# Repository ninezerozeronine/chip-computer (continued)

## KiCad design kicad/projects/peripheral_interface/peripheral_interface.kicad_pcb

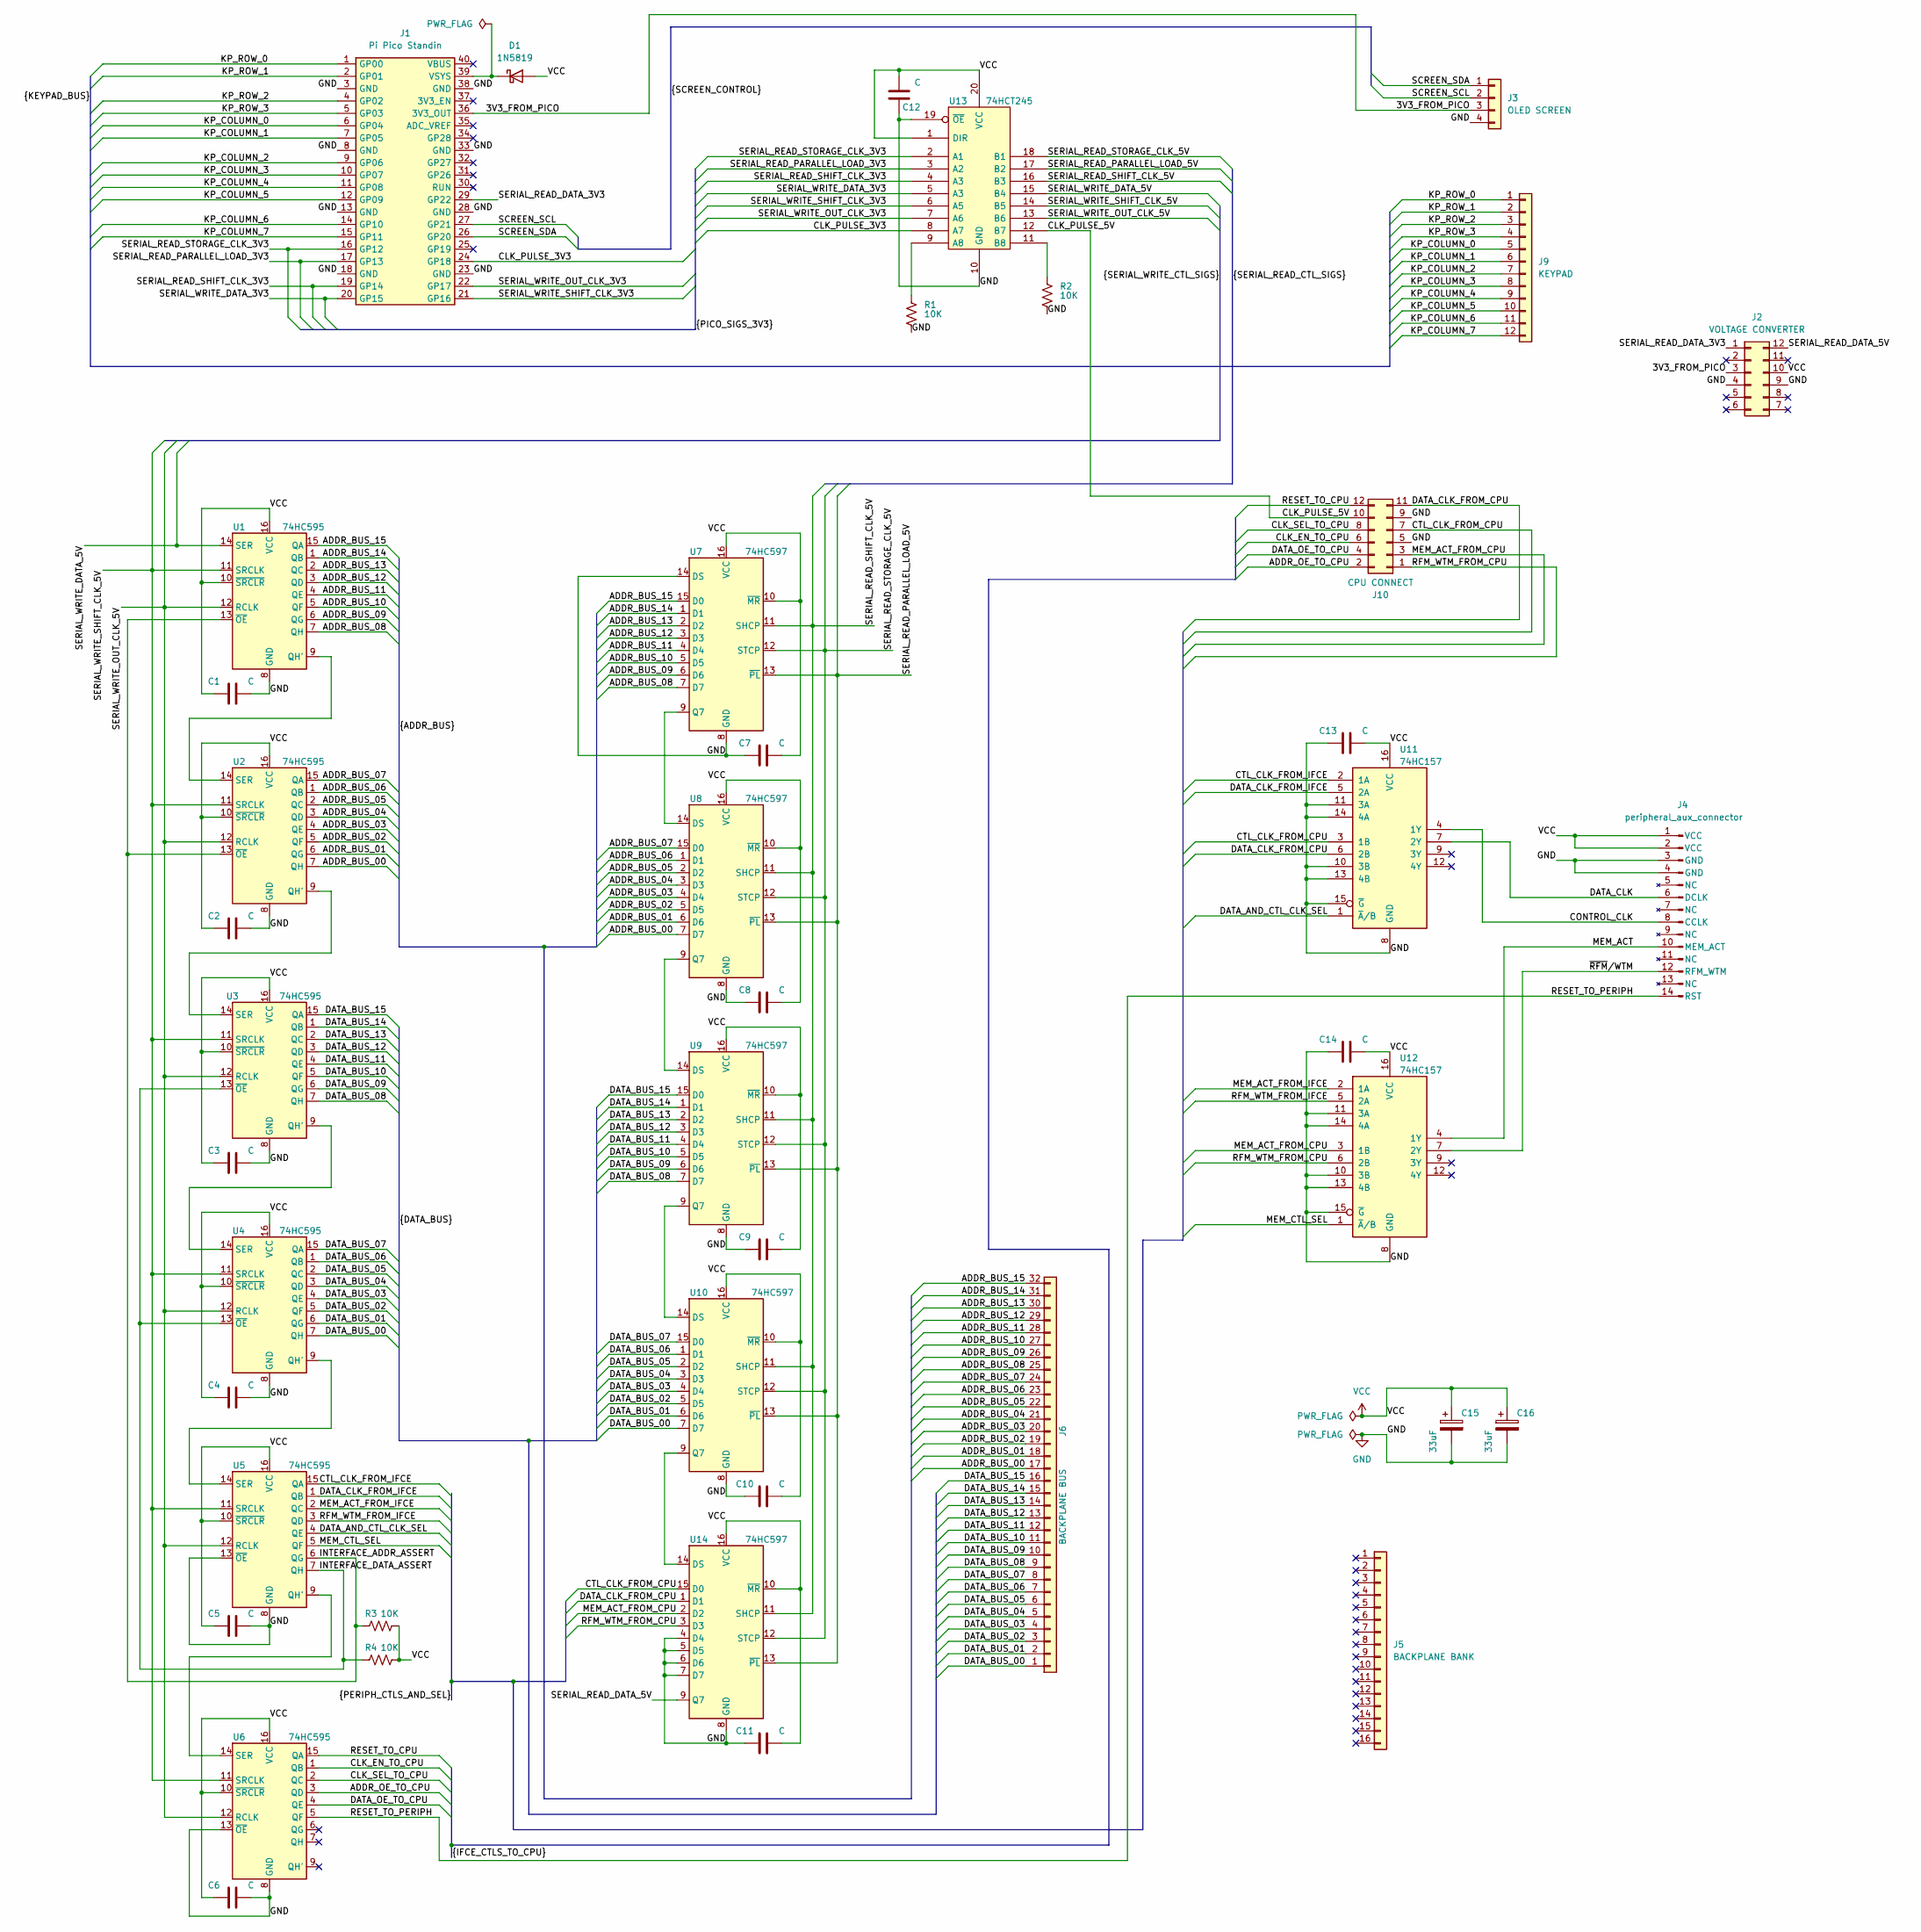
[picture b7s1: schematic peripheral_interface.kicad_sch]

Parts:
C1, C2, C3, C4, C5, C6, C7, C8, C9, C10, C11, C12, C13, C14: C; C_Disc_D4.7mm_W2.5mm_P5.00mm
C15, C16: 33uF; CP_Radial_D6.3mm_P2.50mm
D1: 1N5819; D_DO-41_SOD81_P10.16mm_Horizontal
J1: Pi Pico Standin; pi-pico-standin
J2: VOLTAGE CONVERTER; voltage-level-converter
J3: OLED SCREEN; mini-oled-screen
J4: peripheral_aux_connector; peripheral-backplane-aux
J5: BACKPLANE BANK; peripheral-backplane-membank
J6: BACKPLANE BUS; peripheral-backplane-data-addr-anno
J9: KEYPAD; PinSocket_1x12_P2.54mm_Vertical
J10: CPU CONNECT; PinSocket_2x06_P2.54mm_Horizontal
R1, R2: 10K; R_Axial_DIN0207_L6.3mm_D2.5mm_P10.16mm_Horizontal
R3, R4: 10K; R_Axial_DIN0207_L6.3mm_D2.5mm_P2.54mm_Vertical
U1, U2, U3, U4, U5, U6: 74HC595; DIP-16_W7.62mm_Socket
U7, U8, U9, U10, U14: 74HC597; DIP-16_W7.62mm_Socket
U11, U12: 74HC157; DIP-16_W7.62mm_Socket
U13: 74HCT245; DIP-20_W7.62mm_Socket

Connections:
/3V3_FROM_PICO: J1.36 (3V3_OUT), J2.3, J3.3
/ADDR_BUS_00: J6.17, U2.7 (QH), U8.7 (D7)
/ADDR_BUS_01: J6.18, U2.6 (QG), U8.6 (D6)
/ADDR_BUS_02: J6.19, U2.5 (QF), U8.5 (D5)
/ADDR_BUS_03: J6.20, U2.4 (QE), U8.4 (D4)
/ADDR_BUS_04: J6.21, U2.3 (QD), U8.3 (D3)
/ADDR_BUS_05: J6.22, U2.2 (QC), U8.2 (D2)
/ADDR_BUS_06: J6.23, U2.1 (QB), U8.1 (D1)
/ADDR_BUS_07: J6.24, U2.15 (QA), U8.15 (D0)
/ADDR_BUS_08: J6.25, U1.7 (QH), U7.7 (D7)
/ADDR_BUS_09: J6.26, U1.6 (QG), U7.6 (D6)
/ADDR_BUS_10: J6.27, U1.5 (QF), U7.5 (D5)
/ADDR_BUS_11: J6.28, U1.4 (QE), U7.4 (D4)
/ADDR_BUS_12: J6.29, U1.3 (QD), U7.3 (D3)
/ADDR_BUS_13: J6.30, U1.2 (QC), U7.2 (D2)
/ADDR_BUS_14: J6.31, U1.1 (QB), U7.1 (D1)
/ADDR_BUS_15: J6.32, U1.15 (QA), U7.15 (D0)
/ADDR_OE_TO_CPU: J10.2, U6.3 (QD)
/CLK_EN_TO_CPU: J10.6, U6.1 (QB)
/CLK_PULSE_3V3: J1.24 (GP18), U13.8 (A7)
/CLK_PULSE_5V: J10.10, U13.12 (B7)
/CLK_SEL_TO_CPU: J10.8, U6.2 (QC)
/CONTROL_CLK: J4.8 (CCLK), U11.4 (1Y)
/CTL_CLK_FROM_CPU: J10.7, U11.3 (1B), U14.15 (D0)
/CTL_CLK_FROM_IFCE: U5.15 (QA), U11.2 (1A)
/DATA_AND_CTL_CLK_SEL: U5.4 (QE), U11.1 (~A/B)
/DATA_BUS_00: J6.1, U4.7 (QH), U10.7 (D7)
/DATA_BUS_01: J6.2, U4.6 (QG), U10.6 (D6)
/DATA_BUS_02: J6.3, U4.5 (QF), U10.5 (D5)
/DATA_BUS_03: J6.4, U4.4 (QE), U10.4 (D4)
/DATA_BUS_04: J6.5, U4.3 (QD), U10.3 (D3)
/DATA_BUS_05: J6.6, U4.2 (QC), U10.2 (D2)
/DATA_BUS_06: J6.7, U4.1 (QB), U10.1 (D1)
/DATA_BUS_07: J6.8, U4.15 (QA), U10.15 (D0)
/DATA_BUS_08: J6.9, U3.7 (QH), U9.7 (D7)
/DATA_BUS_09: J6.10, U3.6 (QG), U9.6 (D6)
/DATA_BUS_10: J6.11, U3.5 (QF), U9.5 (D5)
/DATA_BUS_11: J6.12, U3.4 (QE), U9.4 (D4)
/DATA_BUS_12: J6.13, U3.3 (QD), U9.3 (D3)
/DATA_BUS_13: J6.14, U3.2 (QC), U9.2 (D2)
/DATA_BUS_14: J6.15, U3.1 (QB), U9.1 (D1)
/DATA_BUS_15: J6.16, U3.15 (QA), U9.15 (D0)
/DATA_CLK: J4.6 (DCLK), U11.7 (2Y)
/DATA_CLK_FROM_CPU: J10.11, U11.6 (2B), U14.1 (D1)
/DATA_CLK_FROM_IFCE: U5.1 (QB), U11.5 (2A)
/DATA_OE_TO_CPU: J10.4, U6.4 (QE)
/INTERFACE_ADDR_ASSERT: R3.1, U1.13 (~OE), U2.13 (~OE), U5.6 (QG)
/INTERFACE_DATA_ASSERT: R4.1, U3.13 (~OE), U4.13 (~OE), U5.7 (QH)
/KP_COLUMN_0: J1.6 (GP04), J9.5
/KP_COLUMN_1: J1.7 (GP05), J9.6
/KP_COLUMN_2: J1.9 (GP06), J9.7
/KP_COLUMN_3: J1.10 (GP07), J9.8
/KP_COLUMN_4: J1.11 (GP08), J9.9
/KP_COLUMN_5: J1.12 (GP09), J9.10
/KP_COLUMN_6: J1.14 (GP10), J9.11
/KP_COLUMN_7: J1.15 (GP11), J9.12
/KP_ROW_0: J1.1 (GP00), J9.1
/KP_ROW_1: J1.2 (GP01), J9.2
/KP_ROW_2: J1.4 (GP02), J9.3
/KP_ROW_3: J1.5 (GP03), J9.4
/MEM_ACT: J4.10 (MEM_ACT), U12.4 (1Y)
/MEM_ACT_FROM_CPU: J10.3, U12.3 (1B), U14.2 (D2)
/MEM_ACT_FROM_IFCE: U5.2 (QC), U12.2 (1A)
/MEM_CTL_SEL: U5.5 (QF), U12.1 (~A/B)
/RESET_TO_CPU: J10.12, U6.15 (QA)
/RESET_TO_PERIPH: J4.14 (RST), U6.5 (QF)
/RFM_WTM_FROM_CPU: J10.1, U12.6 (2B), U14.3 (D3)
/RFM_WTM_FROM_IFCE: U5.3 (QD), U12.5 (2A)
/SCREEN_SCL: J1.27 (GP21), J3.2
/SCREEN_SDA: J1.26 (GP20), J3.1
/SERIAL_READ_DATA_3V3: J1.29 (GP22), J2.1
/SERIAL_READ_DATA_5V: J2.12, U14.9 (Q7)
/SERIAL_READ_PARALLEL_LOAD_3V3: J1.17 (GP13), U13.3 (A2)
/SERIAL_READ_PARALLEL_LOAD_5V: U7.13 (~PL), U8.13 (~PL), U9.13 (~PL), U10.13 (~PL), U13.17 (B2), U14.13 (~PL)
/SERIAL_READ_SHIFT_CLK_3V3: J1.19 (GP14), U13.4 (A3)
/SERIAL_READ_SHIFT_CLK_5V: U7.11 (SHCP), U8.11 (SHCP), U9.11 (SHCP), U10.11 (SHCP), U13.16 (B3), U14.11 (SHCP)
/SERIAL_READ_STORAGE_CLK_3V3: J1.16 (GP12), U13.2 (A1)
/SERIAL_READ_STORAGE_CLK_5V: U7.12 (STCP), U8.12 (STCP), U9.12 (STCP), U10.12 (STCP), U13.18 (B1), U14.12 (STCP)
/SERIAL_WRITE_DATA_3V3: J1.20 (GP15), U13.5 (A3)
/SERIAL_WRITE_DATA_5V: U1.14 (SER), U13.15 (B4)
/SERIAL_WRITE_OUT_CLK_3V3: J1.22 (GP17), U13.7 (A6)
/SERIAL_WRITE_OUT_CLK_5V: U1.12 (RCLK), U2.12 (RCLK), U3.12 (RCLK), U4.12 (RCLK), U5.12 (RCLK), U6.12 (RCLK), U13.13 (B6)
/SERIAL_WRITE_SHIFT_CLK_3V3: J1.21 (GP16), U13.6 (A5)
/SERIAL_WRITE_SHIFT_CLK_5V: U1.11 (SRCLK), U2.11 (SRCLK), U3.11 (SRCLK), U4.11 (SRCLK), U5.11 (SRCLK), U6.11 (SRCLK), U13.14 (B5)
/~RFM/WTM: J4.12 (RFM_WTM), U12.7 (2Y)
GND: C1.2, C2.2, C3.2, C4.2, C5.2, C6.2, C7.1, C8.1, C9.1, C10.1, C11.1, C12.1, C13.1, C14.1, C15.2, C16.2, J1.3 (GND), J1.8 (GND), J1.13 (GND), J1.18 (GND), J1.23 (GND), J1.28 (GND), J1.33 (GND), J1.38 (GND), J2.4, J2.9, J3.4, J4.3 (GND), J4.4 (GND), J10.5, J10.9, R1.2, R2.2, U1.8 (GND), U2.8 (GND), U3.8 (GND), U4.8 (GND), U5.8 (GND), U5.13 (~OE), U6.8 (GND), U6.13 (~OE), U7.8 (GND), U7.14 (DS), U8.8 (GND), U9.8 (GND), U10.8 (GND), U11.8 (GND), U11.10 (3B), U11.11 (3A), U11.13 (4B), U11.14 (4A), U11.15 (~G), U12.8 (GND), U12.10 (3B), U12.11 (3A), U12.13 (4B), U12.14 (4A), U12.15 (~G), U13.10 (GND), U13.19 (~OE), U14.4 (D4), U14.5 (D5), U14.6 (D6), U14.7 (D7), U14.8 (GND)
unnamed: D1.1 (K), J1.39 (VSYS)
unnamed: U1.9 (QH'), U2.14 (SER)
unnamed: U2.9 (QH'), U3.14 (SER)
unnamed: U3.9 (QH'), U4.14 (SER)
unnamed: U4.9 (QH'), U5.14 (SER)
unnamed: U5.9 (QH'), U6.14 (SER)
unnamed: U7.9 (Q7), U8.14 (DS)
unnamed: U8.9 (Q7), U9.14 (DS)
unnamed: U9.9 (Q7), U10.14 (DS)
unnamed: U10.9 (Q7), U14.14 (DS)
unnamed: R1.1, U13.9 (A8)
unnamed: R2.1, U13.11 (B8)
VCC: C1.1, C2.1, C3.1, C4.1, C5.1, C6.1, C7.2, C8.2, C9.2, C10.2, C11.2, C12.2, C13.2, C14.2, C15.1, C16.1, D1.2 (A), J2.10, J4.1 (VCC), J4.2 (VCC), R3.2, R4.2, U1.10 (~SRCLR), U1.16 (VCC), U2.10 (~SRCLR), U2.16 (VCC), U3.10 (~SRCLR), U3.16 (VCC), U4.10 (~SRCLR), U4.16 (VCC), U5.10 (~SRCLR), U5.16 (VCC), U6.10 (~SRCLR), U6.16 (VCC), U7.10 (~MR), U7.16 (VCC), U8.10 (~MR), U8.16 (VCC), U9.10 (~MR), U9.16 (VCC), U10.10 (~MR), U10.16 (VCC), U11.16 (VCC), U12.16 (VCC), U13.1 (DIR), U13.20 (VCC), U14.10 (~MR), U14.16 (VCC)

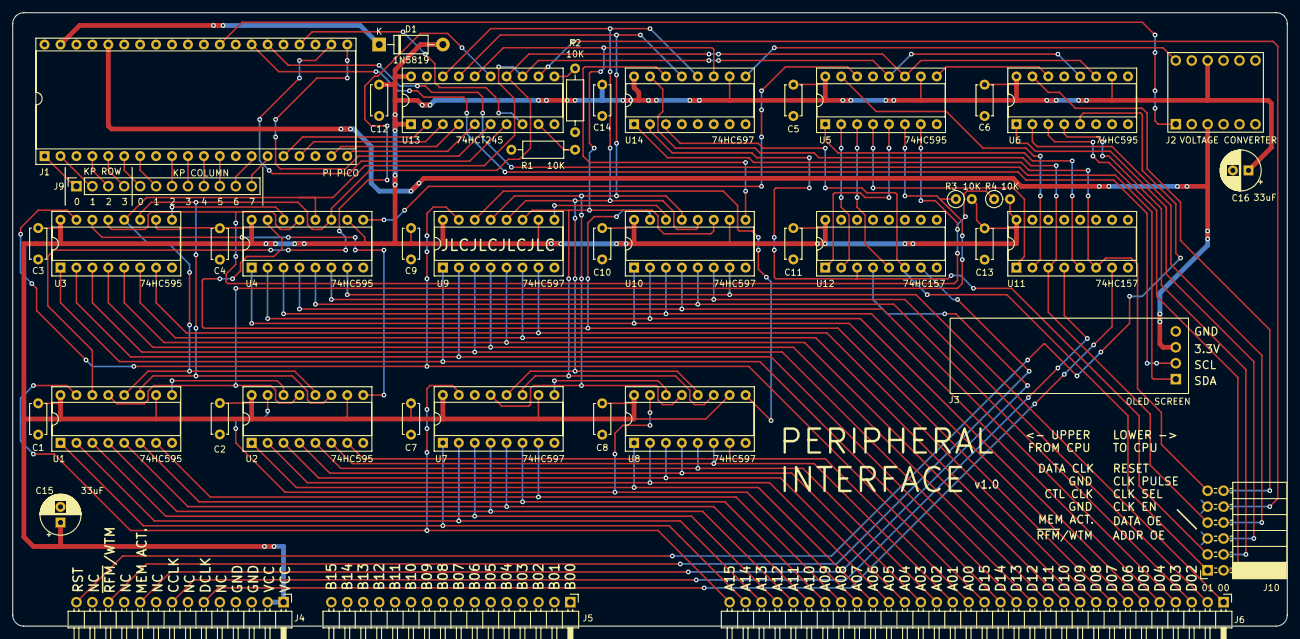
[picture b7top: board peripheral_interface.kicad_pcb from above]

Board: 2 copper layers, 203.2 x 97.8 mm, 43 parts (0 on the bottom side), 99 nets.

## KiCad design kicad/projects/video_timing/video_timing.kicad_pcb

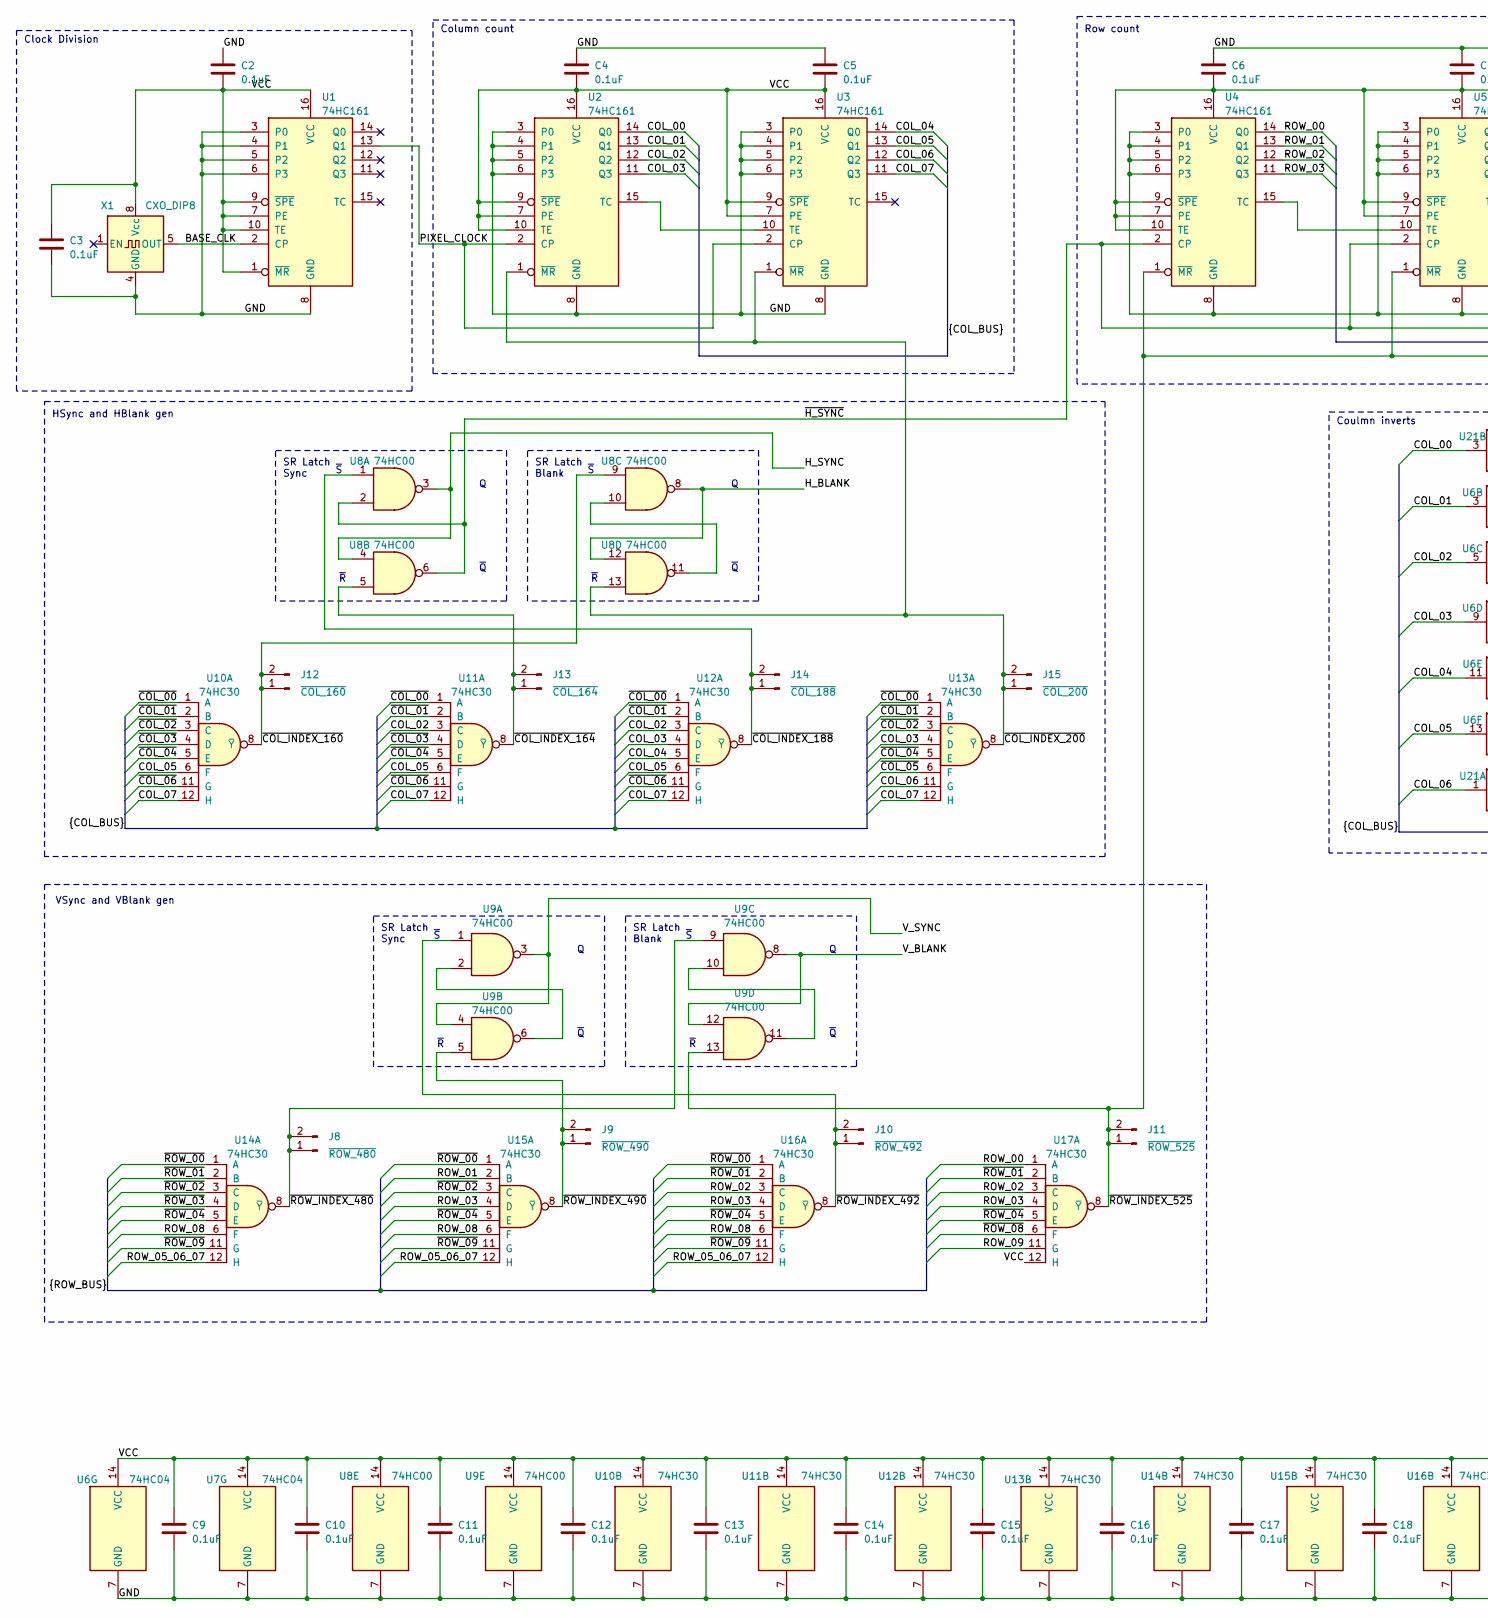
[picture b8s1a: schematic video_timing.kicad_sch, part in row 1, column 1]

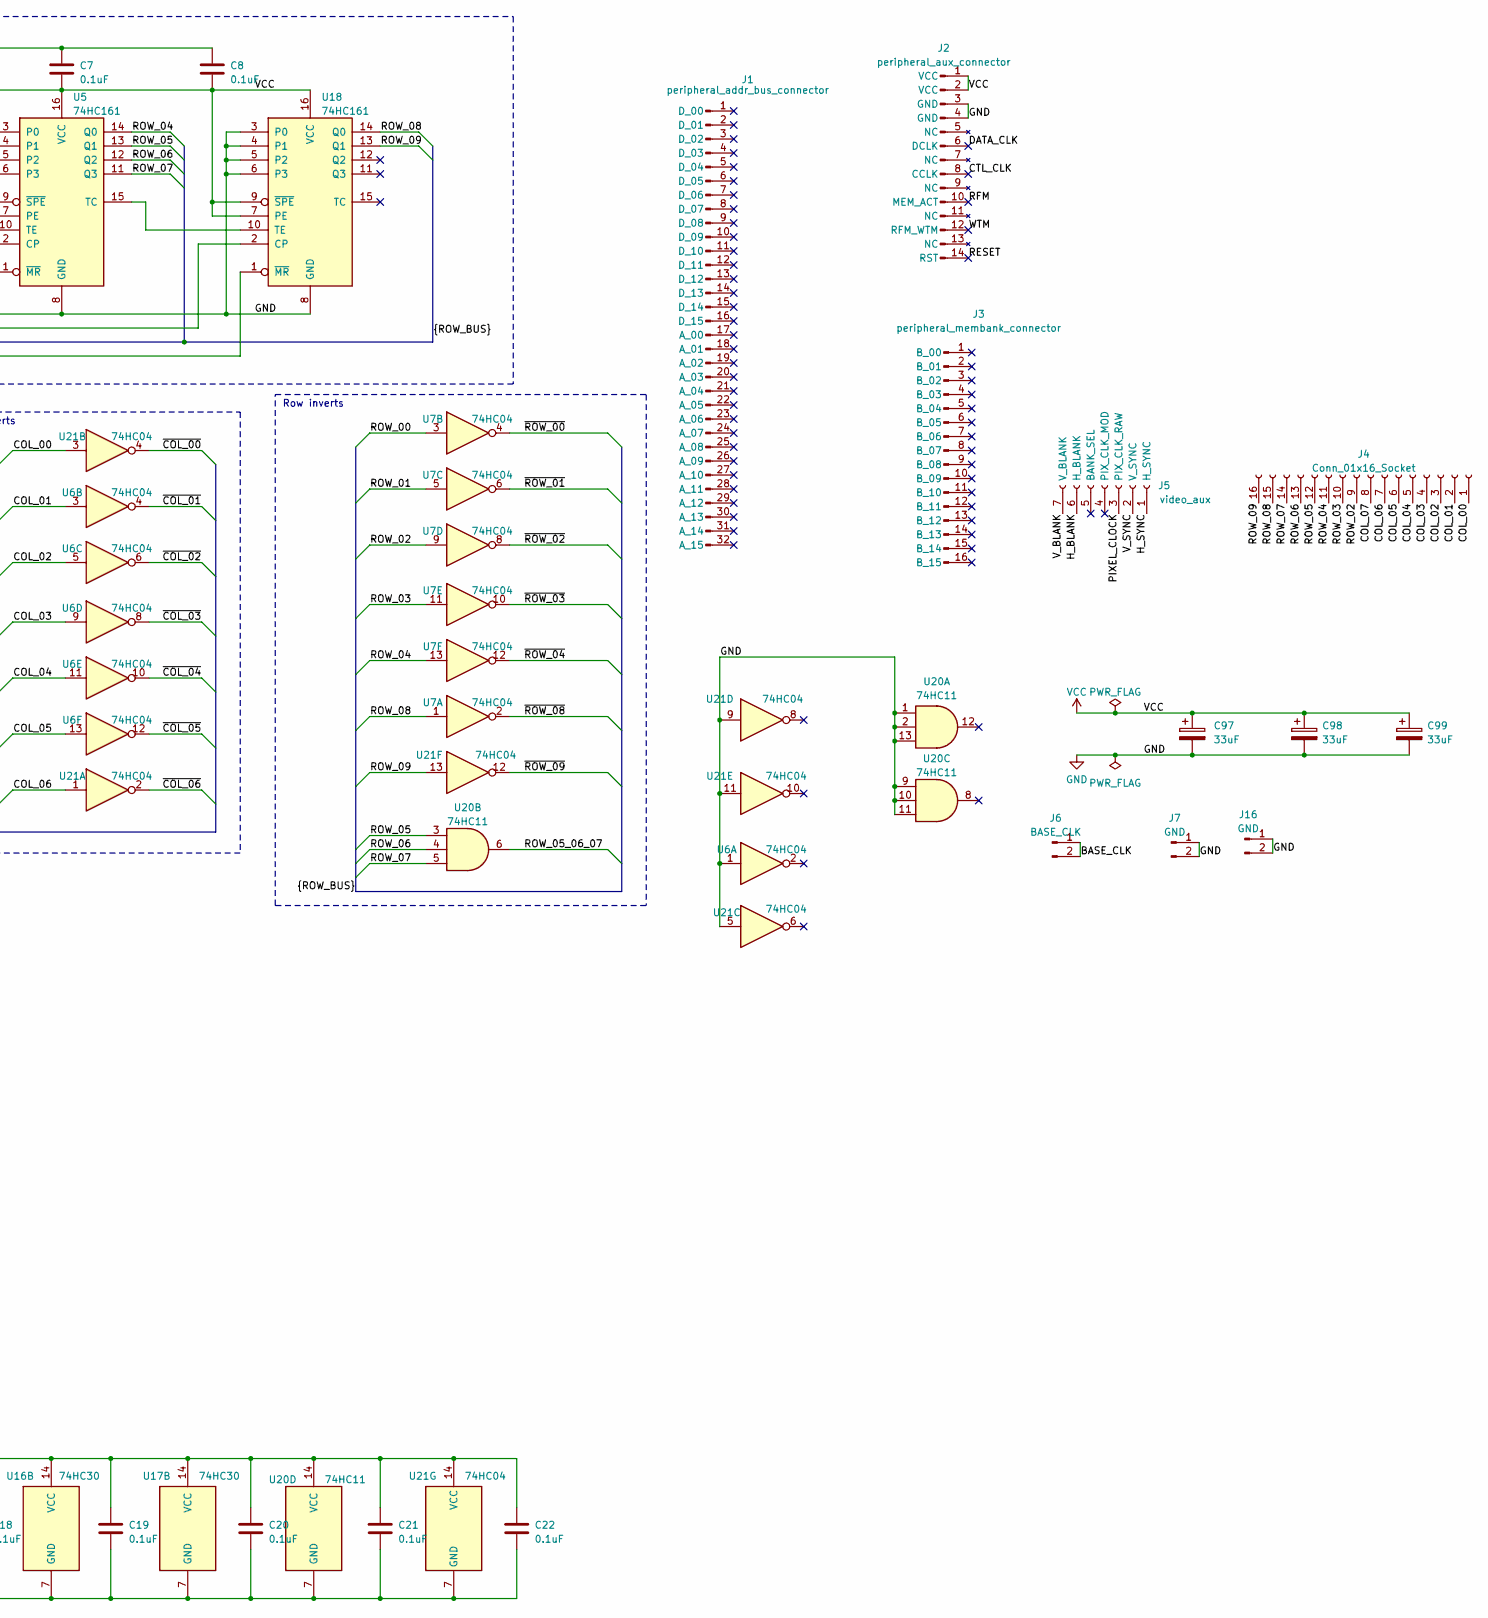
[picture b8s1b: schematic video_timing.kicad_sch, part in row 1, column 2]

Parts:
C2, C3, C4, C5, C6, C7, C8, C9, C10, C11, C12, C13, C14, C15, C16, C17, C18, C19, C20, C21, C22: 0.1uF; C_Disc_D5.0mm_W2.5mm_P5.00mm
C97, C98, C99: 33uF; CP_Radial_D6.3mm_P2.50mm
J1: peripheral_addr_bus_connector; peripheral-backplane-data-addr-anno
J2: peripheral_aux_connector; peripheral-backplane-aux
J3: peripheral_membank_connector; peripheral-backplane-membank
J4: Conn_01x16_Socket; PinSocket_1x16_P2.54mm_Horizontal
J5: video_aux; PinSocket_1x07_P2.54mm_Horizontal
J6: BASE_CLK; PinHeader_1x02_P2.54mm_Vertical
J7, J16: GND; PinHeader_1x02_P2.54mm_Vertical
J8: ~{ROW_480}; PinHeader_1x02_P2.54mm_Vertical
J9: ~{ROW_490}; PinHeader_1x02_P2.54mm_Vertical
J10: ~{ROW_492}; PinHeader_1x02_P2.54mm_Vertical
J11: ~{ROW_525}; PinHeader_1x02_P2.54mm_Vertical
J12: ~{COL_160}; PinHeader_1x02_P2.54mm_Vertical
J13: ~{COL_164}; PinHeader_1x02_P2.54mm_Vertical
J14: ~{COL_188}; PinHeader_1x02_P2.54mm_Vertical
J15: ~{COL_200}; PinHeader_1x02_P2.54mm_Vertical
U1, U2, U3, U4, U5, U18: 74HC161; DIP-16_W7.62mm_Socket
U6, U7, U21: 74HC04; DIP-14_W7.62mm_Socket
U8, U9: 74HC00; DIP-14_W7.62mm_Socket
U10, U11, U12, U13, U14, U15, U16, U17: 74HC30; DIP-14_W7.62mm_Socket
U20: 74HC11; DIP-14_W7.62mm_Socket
X1: CXO_DIP8; Oscillator_DIP-8

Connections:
/BASE_CLK: J6.1, J6.2, U1.2 (CP), X1.5 (OUT)
/COL_00: J4.1, U2.14 (Q0), U21.3
/COL_01: J4.2, U2.13 (Q1), U6.3
/COL_02: J4.3, U2.12 (Q2), U6.5, U11.3 (C), U12.3 (C)
/COL_03: J4.4, U2.11 (Q3), U6.9, U12.4 (D), U13.4 (D)
/COL_04: J4.5, U3.14 (Q0), U6.11, U12.5 (E)
/COL_05: J4.6, U3.13 (Q1), U6.13, U10.6 (F), U11.6 (F), U12.6 (F)
/COL_06: J4.7, U3.12 (Q2), U13.11 (G), U21.1
/COL_07: J4.8, U3.11 (Q3), U10.12 (H), U11.12 (H), U12.12 (H), U13.12 (H)
/CTL_CLK: J2.8 (CCLK)
/DATA_CLK: J2.6 (DCLK)
/H_BLANK: J5.6 (H_BLANK), U8.8, U8.12
/H_SYNC: J5.1 (H_SYNC), U8.3, U8.4
/PIXEL_CLOCK: J5.3 (PIX_CLK_RAW), U1.13 (Q1), U2.2 (CP), U3.2 (CP)
/RESET: J2.14 (RST)
/RFM: J2.10 (MEM_ACT)
/ROW_00: U4.14 (Q0), U7.3, U17.1 (A)
/ROW_01: U4.13 (Q1), U7.5, U15.2 (B)
/ROW_02: J4.9, U4.12 (Q2), U7.9, U16.3 (C), U17.3 (C)
/ROW_03: J4.10, U4.11 (Q3), U7.11, U15.4 (D), U16.4 (D), U17.4 (D)
/ROW_04: J4.11, U5.14 (Q0), U7.13
/ROW_05: J4.12, U5.13 (Q1), U20.3
/ROW_05_06_07: U14.12 (H), U15.12 (H), U16.12 (H), U20.6
/ROW_06: J4.13, U5.12 (Q2), U20.4
/ROW_07: J4.14, U5.11 (Q3), U20.5
/ROW_08: J4.15, U7.1, U14.6 (F), U15.6 (F), U16.6 (F), U18.14 (Q0)
/ROW_09: J4.16, U17.11 (G), U18.13 (Q1), U21.13
/V_BLANK: J5.7 (V_BLANK), U9.8, U9.12
/V_SYNC: J5.2 (V_SYNC), U9.3, U9.4
/WTM: J2.12 (RFM_WTM)
/~COL_00: U10.1 (A), U11.1 (A), U12.1 (A), U13.1 (A), U21.4
/~COL_01: U6.4, U10.2 (B), U11.2 (B), U12.2 (B), U13.2 (B)
/~COL_02: U6.6, U10.3 (C), U13.3 (C)
/~COL_03: U6.8, U10.4 (D), U11.4 (D)
/~COL_04: U6.10, U10.5 (E), U11.5 (E), U13.5 (E)
/~COL_05: U6.12, U13.6 (F)
/~COL_06: U10.11 (G), U11.11 (G), U12.11 (G), U21.2
/~COL_INDEX_160: J12.1, J12.2, U8.9, U10.8 (~Y)
/~COL_INDEX_164: J13.1, J13.2, U8.5, U11.8 (~Y)
/~COL_INDEX_188: J14.1, J14.2, U8.1, U12.8 (~Y)
/~COL_INDEX_200: J15.1, J15.2, U2.1 (~MR), U3.1 (~MR), U8.13, U13.8 (~Y)
/~H_SYNC: U4.2 (CP), U5.2 (CP), U8.2, U8.6, U18.2 (CP)
/~ROW_00: U7.4, U14.1 (A), U15.1 (A), U16.1 (A)
/~ROW_01: U7.6, U14.2 (B), U16.2 (B), U17.2 (B)
/~ROW_02: U7.8, U14.3 (C), U15.3 (C)
/~ROW_03: U7.10, U14.4 (D)
/~ROW_04: U7.12, U14.5 (E), U15.5 (E), U16.5 (E), U17.5 (E)
/~ROW_08: U7.2, U17.6 (F)
/~ROW_09: U14.11 (G), U15.11 (G), U16.11 (G), U21.12
/~ROW_INDEX_480: J8.1, J8.2, U9.9, U14.8 (~Y)
/~ROW_INDEX_490: J9.1, J9.2, U9.5, U15.8 (~Y)
/~ROW_INDEX_492: J10.1, J10.2, U9.1, U16.8 (~Y)
/~ROW_INDEX_525: J11.1, J11.2, U4.1 (~MR), U5.1 (~MR), U9.13, U17.8 (~Y), U18.1 (~MR)
GND: C2.1, C3.2, C4.1, C5.1, C6.1, C7.1, C8.1, C9.2, C10.2, C11.2, C12.2, C13.2, C14.2, C15.2, C16.2, C17.2, C18.2, C19.2, C20.2, C21.2, C22.2, C97.2, C98.2, C99.2, J2.3 (GND), J2.4 (GND), J7.1, J7.2, J16.1, J16.2, U1.3 (P0), U1.4 (P1), U1.5 (P2), U1.6 (P3), U1.8 (GND), U2.3 (P0), U2.4 (P1), U2.5 (P2), U2.6 (P3), U2.8 (GND), U3.3 (P0), U3.4 (P1), U3.5 (P2), U3.6 (P3), U3.8 (GND), U4.3 (P0), U4.4 (P1), U4.5 (P2), U4.6 (P3), U4.8 (GND), U5.3 (P0), U5.4 (P1), U5.5 (P2), U5.6 (P3), U5.8 (GND), U6.1, U6.7 (GND), U7.7 (GND), U8.7 (GND), U9.7 (GND), U10.7 (GND), U11.7 (GND), U12.7 (GND), U13.7 (GND), U14.7 (GND), U15.7 (GND), U16.7 (GND), U17.7 (GND), U18.3 (P0), U18.4 (P1), U18.5 (P2), U18.6 (P3), U18.8 (GND), U20.1, U20.2, U20.7 (GND), U20.9, U20.10, U20.11, U20.13, U21.5, U21.7 (GND), U21.9, U21.11, X1.4 (GND)
unnamed: U2.15 (TC), U3.10 (TE)
unnamed: U4.15 (TC), U5.10 (TE)
unnamed: U8.10, U8.11
unnamed: U9.2, U9.6
unnamed: U9.10, U9.11
unnamed: U5.15 (TC), U18.10 (TE)
VCC: C2.2, C3.1, C4.2, C5.2, C6.2, C7.2, C8.2, C9.1, C10.1, C11.1, C12.1, C13.1, C14.1, C15.1, C16.1, C17.1, C18.1, C19.1, C20.1, C21.1, C22.1, C97.1, C98.1, C99.1, J2.1 (VCC), J2.2 (VCC), U1.1 (~MR), U1.7 (PE), U1.9 (~SPE), U1.10 (TE), U1.16 (VCC), U2.7 (PE), U2.9 (~SPE), U2.10 (TE), U2.16 (VCC), U3.7 (PE), U3.9 (~SPE), U3.16 (VCC), U4.7 (PE), U4.9 (~SPE), U4.10 (TE), U4.16 (VCC), U5.7 (PE), U5.9 (~SPE), U5.16 (VCC), U6.14 (VCC), U7.14 (VCC), U8.14 (VCC), U9.14 (VCC), U10.14 (VCC), U11.14 (VCC), U12.14 (VCC), U13.14 (VCC), U14.14 (VCC), U15.14 (VCC), U16.14 (VCC), U17.12 (H), U17.14 (VCC), U18.7 (PE), U18.9 (~SPE), U18.16 (VCC), U20.14 (VCC), U21.14 (VCC), X1.8 (Vcc)

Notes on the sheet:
~{R}
SR Latch Sync
~{S}
~{Q}
Row count
SR Latch Blank
Column count
Coulmn inverts
VSync and VBlank gen
Row inverts
Clock Division
HSync and HBlank gen

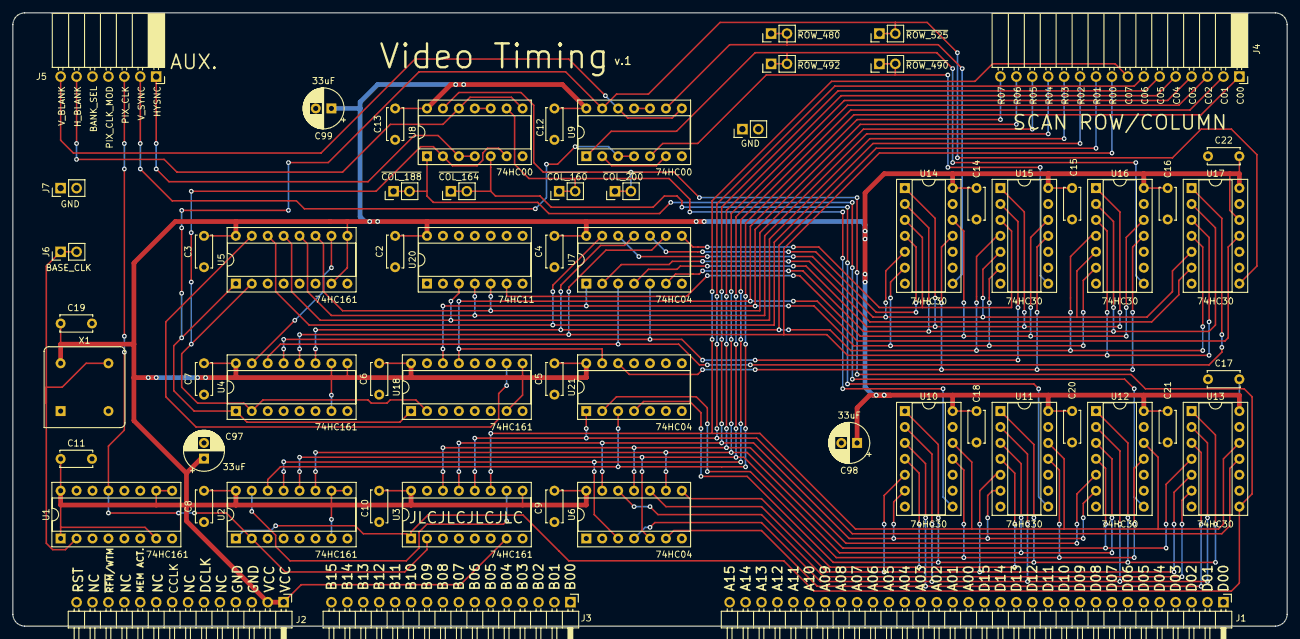
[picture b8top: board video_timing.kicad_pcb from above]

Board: 2 copper layers, 203.2 x 97.8 mm, 61 parts (0 on the bottom side), 56 nets.

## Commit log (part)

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2022-06-21 Add copy operation.
2022-06-24 Start on JUMP_IF_EQ_ZERO operation.
2022-06-27 Add jump operation.
2022-06-30 Add set operation.
2022-07-04 Stop Labels binding to variables. Add more JUMP options. Add more to test program. Remove PC as argument for some instructions.
2022-07-05 Actually add copy assembly tests, correct a few errors in other tests. Last commit was just sandbox
2022-07-09 Add missing instruction signautres as comments.
2022-07-09 Add incr and decr operations.
2022-07-11 Add push and pop. Move load and store test generation into test utils.
2022-07-15 Add ROT_LEFT op and re-order test_sixteen.
2022-07-15 Add ROT_LEFT test.
2022-07-15 Add call tester in assembly test program.
2022-07-17 Finish adding Jump if acc comparison ops.
2022-07-18 Dummy change.
2022-07-19 Fix bad comparison logic thanks to slightly vague 74LS181 datasheet.
2022-07-22 Rename op modules with xs to more explicit names.
2022-07-24 Remove rescue libs.
2022-07-24 Switch to HC series chips and fix some labelling in program counter or register PCB.
2022-07-24 Update position of bottom connectors on register.
2022-07-24 Move alu res flags lower connectors.
2022-07-24 Adjust lower connector position on control unit.
2022-07-25 Turn on layer vis on ALU.
2022-07-26 Finish ALU input buffers.
2022-08-01 Add top power and LED control jumper to ALU.
2022-08-01 Add top power and LED control to control unit.
2022-08-01 Better labels on ALU. Top power and LED control on register.
2022-08-01 Bring in interface and CPU status boards from eariler branch.
2022-08-26 Experiments with sockets in qt and asyncio. Rough out the front panel and interface classes.
2022-08-30 Interface pretty much done. Need to add better modes to front panel.
2022-09-01 Run some tests sending data between qt and asyncio sockets.
2022-09-12 Lots of changes to micropython - front panel gearing up for keypad.
2022-10-10 Front panel and interface tested without additional interface hardware.
2022-10-17 PCB work for interface.
2022-10-21 Most of interface positioning complete.
2022-10-25 Bit of wiring on the CPU status board.
2022-10-26 Added power port and LED control to status board.
2022-11-04 Labelling on CPU status.
2022-11-07 Finish off CPU status.
2022-11-12 Logisim is very sad now - lots of errors
2022-11-12 Fixed logisim errors - silly pulldown resistors...
2022-11-12 Add pullup resistors on bus output enables and space tracks slightly on register.
2022-11-13 Add pullup on bus out on program counter and update LED control.
2022-11-19 simplify clock in logisim.
2022-11-20 Add HC109 chip. Add simpler clock and reset delay to interface. Need to lay out on PCB.
2022-11-28 Last bits of labelling and re-routing on interface-clock
2022-11-28 Tech checks on ALU.
2022-11-30 Control Unit Tech checks.
2022-12-01 Tech checks on interface, some of program counter.
2022-12-04 Program counter tech checks complete, starting IDC addition to interface.
2022-12-04 Tech checks complete on program counter.
2022-12-05 Added ECNZ to CPU Status.
2022-12-07 Finish adding pull downs to inputs and doing tech checks.
2022-12-07 Part way through spacing and tech checking register.
2022-12-08 Alu tech checks.
2022-12-08 CPU status tech checked.
2022-12-08 Finish spacing on program counter.
2022-12-09 interface tech checked.
2022-12-09 Last tweak - move old gerbers out of the way.
2022-12-09 Part way through generating gerbers. Updated control unit chips to be sockets.
2022-12-10 This is the 2.0 commit that the boards were sent from
2023-01-12 Generate new ROMS. Add fritzing design files for RAM.
2023-01-12 Add clock enable on CPU output for front panel. Adjust clock freq. compensation. Add 16 bit fibb program in micropython.
2023-01-13 Adding changes from test of interface and ram together.
2023-01-21 Update Ctl ad data clockl labelling on interface. Rewrite roms to account for reversed ECNZ on CU.
2023-02-02 Add progress on interface.
2023-02-07 Add latest on perpheral interface.
2023-02-16 Starting on PCB layout for peripheral interface.
2023-02-17 Start laying out PCB and upgrade to KiCad 7.
2023-02-27 More work on peripheral PCB. Added seperate reset lines for CPU and peripherals.
2023-03-06 Routing on Periph interface complete.
2023-03-21 Add peripheral board template.
2023-04-14 Finish off peripheral template.
2023-04-21 RAM schematic 80 percent complete and initial layout of PCB.
2023-04-27 Start laying out RAM wiring.
2023-05-02 Start schematic for ROM and counter.
2023-05-08 most of schematic done for rom counter
2023-05-10 More PCB layout for ROM counter.
2023-05-11 More PCB work on ROM counter.
2023-05-16 PCB for ROM counter done - still needs tech checks
2023-05-21 Rough layout of peripheral connect PCB.
2023-05-29 Updates design rules and constraints in peripheral boards. Make a start on CPU board template.
2023-05-31 Start work on gamepad schematic.
2023-06-05 Start routing gamepad PCB.
2023-06-09 Add gamepad connector and almost complete on gamepad PCB
2023-06-11 Rough in the video timing PCB
2023-06-13 Roughing out the video baords - time to switch to 157s for bank sel as well.
2023-06-16 Tech chekcs on Peripheral connect
2023-06-17 Interface clock updated to single line rfm wtm.
2023-06-17 Peripheral connect updated to one wire rfm wtm.
2023-06-18 Update rom-counter to single singal rfm wtm.
2023-06-18 LED positioning tidy up.
2023-07-07 Start writing draw diagonal line assembly
2023-08-30 Background changes by kicad to interface clock by the looks.
2023-08-31 Update interface clock to allow reading of databus when databus output is disabled.
2023-09-04 Add double row pin socket to peripheral connect.
2023-09-04 Update peripheral interface.
2023-09-04 Peripheral connect updated to support new bus connect.
2023-09-11 Finishing touches on gamepad.
2023-09-13 Tech checks finished on peripheral connect.
2023-09-17 ROM counter tech checked.
2023-09-20 Tech checks on interface clock complete.
2023-09-25 Generate peripheral gerbers.
2023-10-01 Update micropython interface to support seperate CPU and Peripheral resets, and single signal memory direction.
2023-10-15 Fix some grammar errors in micropython.
2023-10-23 Start proof of concept for socket comms.
2023-10-24 Comms back and forth working, but firewall needs to be disabled on windows machine...
2023-10-31 Add assemble and send functionality.
2023-11-02 Controller being read by Computer.
2023-11-03 Add a dummy change
2023-11-05 Add coliision detection
2023-11-06 Add obstacle types
2023-11-06 Add obstacle type drawing.
2023-11-06 Add overhang obstacle.
2023-11-16 Planning for video card.
2023-11-28 Start laying out video timing.
2023-12-01 Add screen draw speed test program.
2023-12-06 Start roughing in video output.
2023-12-29 Add music planning and some extra work planning video card layouts.
2023-12-31 Adding video aux and some bits and bieces on video boards.
2024-01-03 Majority of video timing PCB layout done. Text and labels next.
2024-01-06 Start work on shift status delay PCB.
2024-01-08 Start work on video bank sel cursor.
2024-01-10 Add indicator LEDs to shift status delay board. Bit of work on bank sel PCB.
2024-01-13 Part way through output PCB.
2024-01-13 First pass of output PCB complete.
2024-01-15 Row and column order made consistent on top connectors. Bank Sel cursor tech checked.
2024-01-18 Switched A and B outputs on bank sel. Bit of work on logic and PCB for output. Clarified bank sel 0 and 1 and banks A and B in docs.
2024-01-21 Video output tech checks complete
2024-01-24 Create template for sound card and add 74HC40103 schematic.
2024-01-30 Little bit more work on sounde square.
2024-02-01 Add led output and clock divider to sound square.
2024-02-05 Started on BOMs, made some sounds notes after tests.
2024-02-16 Start converting rom counter to be a 32 bit counter with HC590 counter chips.
2024-02-21 ROM counter v2 tech checks done.
2024-02-23 Change NOR to OR for combining TCs of counters on sound square.
2024-03-08 More work on sound square PCB.
2024-03-14 More work on sound square PCB - what a slog!
2024-03-19 Finishing touches on sound square.
2024-03-22 Last few tech checks - gnd test points and video cursor/scan input switch order for vid output left to check.
2024-03-25 Add software reset on rom counter.
2024-04-02 Start working on Qt connection interface.
2024-04-07 Persisten socket connection prototype and some debugging scripts.
2024-04-14 Job queue with UI seems to be working.
2024-04-14 WIP for micropython job processing and panel display methodology update
2024-04-15 Message comms example now working nicely. Next is to update the existing micropython to follow suit.
2024-04-20 Move UI into src directory and split up into smaller modules.
2024-04-20 Add head and run control.
2024-04-21 Add connection section to UI
2024-04-23 Part way through first all up test of UI to panel comms, need to work on client side.
2024-04-25 Start adding docstrings to new code in network.
2024-04-27 Panel conversion to async complete. Now need to rejig display and add client friendly functions.
2024-04-28 Start work on client UI to make panel calls.
2024-05-14 Most of the client methods on the panel are in place. Need to finish adding keypad controls and test.
2024-05-16 First test of video card with pico control over wifi - drew a smiley face!
2024-05-18 Line numbers and tabs in place for assembler UI
2024-05-19 Add batch read and write to panel (untested). Start on assembly highlighting - woo!
2024-05-21 Add and test incr and decr memory ref instructions.
2024-05-25 Latest for video tests.
2024-06-16 WIP for job manager view in UI.
2024-06-17 Remove all the sleeps in the micropython code.
2024-06-23 Fix a few UI quirks after moving to qtpy and pyside6
2024-06-27 Start working on multi register board.
2024-06-30 Start creating new modules in logisim.
2024-07-05 3 New modules complete, need wiring into CPU now.
2024-07-21 Logisim updated with new modules, ready for microcode updates
2024-07-21 Add new control signals to language defs and clear out some old cruft.
2024-07-21 Update copy ops with new registers
2024-07-21 Update incr decr ops.
2024-07-22 Update call and return ops.
2024-07-22 Tidy up and better variable naming in load store and incr decr.
2024-07-24 Update jump if acc (n) eq ops.
2024-07-24 Update jump if flag ops
2024-07-24 Update jump op
2024-07-25 Update simple ALU ops.
2024-07-25 Add STORE_(IN/DE)CR ops.
2024-07-25 Fix machinecode gen in in incr decr ops.
2024-07-25 Add ACC comparison to value in memory
2024-07-26 New instructions complete.
2024-07-31 Start operations supporting generation of test assembly lines, and seembly to test the instructions.
2024-08-06 Most of the way through moving test assembly code to op modules.
2024-08-08 Add some padding around jumps to halts to help make debugging easier.
2024-08-09 Spelling mistakes corrected in test assembly. New ROMs written but not loaded.
2024-08-18 Test code for new modules complete, tested in logisim and working.
2024-09-11 Schematic mostly done for multi reg
2024-09-12 WIP on multi reg PCB
2024-09-14 Multi reg complete - still needs tech checks.
2024-09-20 More work on presettable counter with offset PCB.
2024-09-25 Roughing in the shift rot schematic and PCB.
2024-09-28 More PCB work on shift rot
2024-10-04 More work on shift rot PCB
2024-10-25 Shift rot pretty much done. Final tidy ups on offset preset counter.
2024-11-02 WIP on status word
2024-11-06 WIP on status word PCB
2024-11-17 Tech check on status word complete
2024-11-17 Multi reg tech checks complete
2024-11-18 Gerbers generated
2024-11-20 Finish updating assembly docs
2024-12-09 Gen roms for new hardware
2024-12-10 Fix execution of uninitialized memory in laod and store tests.
2024-12-11 Test program for video card working. Start docs for video card and status word. Re-organise docs a bit.
2024-12-12 Make new pong file - get skeleton of pong working
2025-01-06 Top and bottom collisions implemented
2025-02-09 Small bit of progress on pong - and the beginnings of the font files.
2025-02-18 Smooth out motion for pong
2025-02-23 Ball bounces on paddle miss for now
2025-02-24 40x30 res working and laid out.
2025-02-26 Message for point scorer.
2025-02-28 Sound working - beep boop beep boop
2025-03-02 Ball trail fades
